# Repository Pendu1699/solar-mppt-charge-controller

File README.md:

# solar-mppt-charge-controller
ESP32-based solar MPPT charge controller, custom PCB, perturb &amp; observe tracking algorithm, logged efficiency test data.

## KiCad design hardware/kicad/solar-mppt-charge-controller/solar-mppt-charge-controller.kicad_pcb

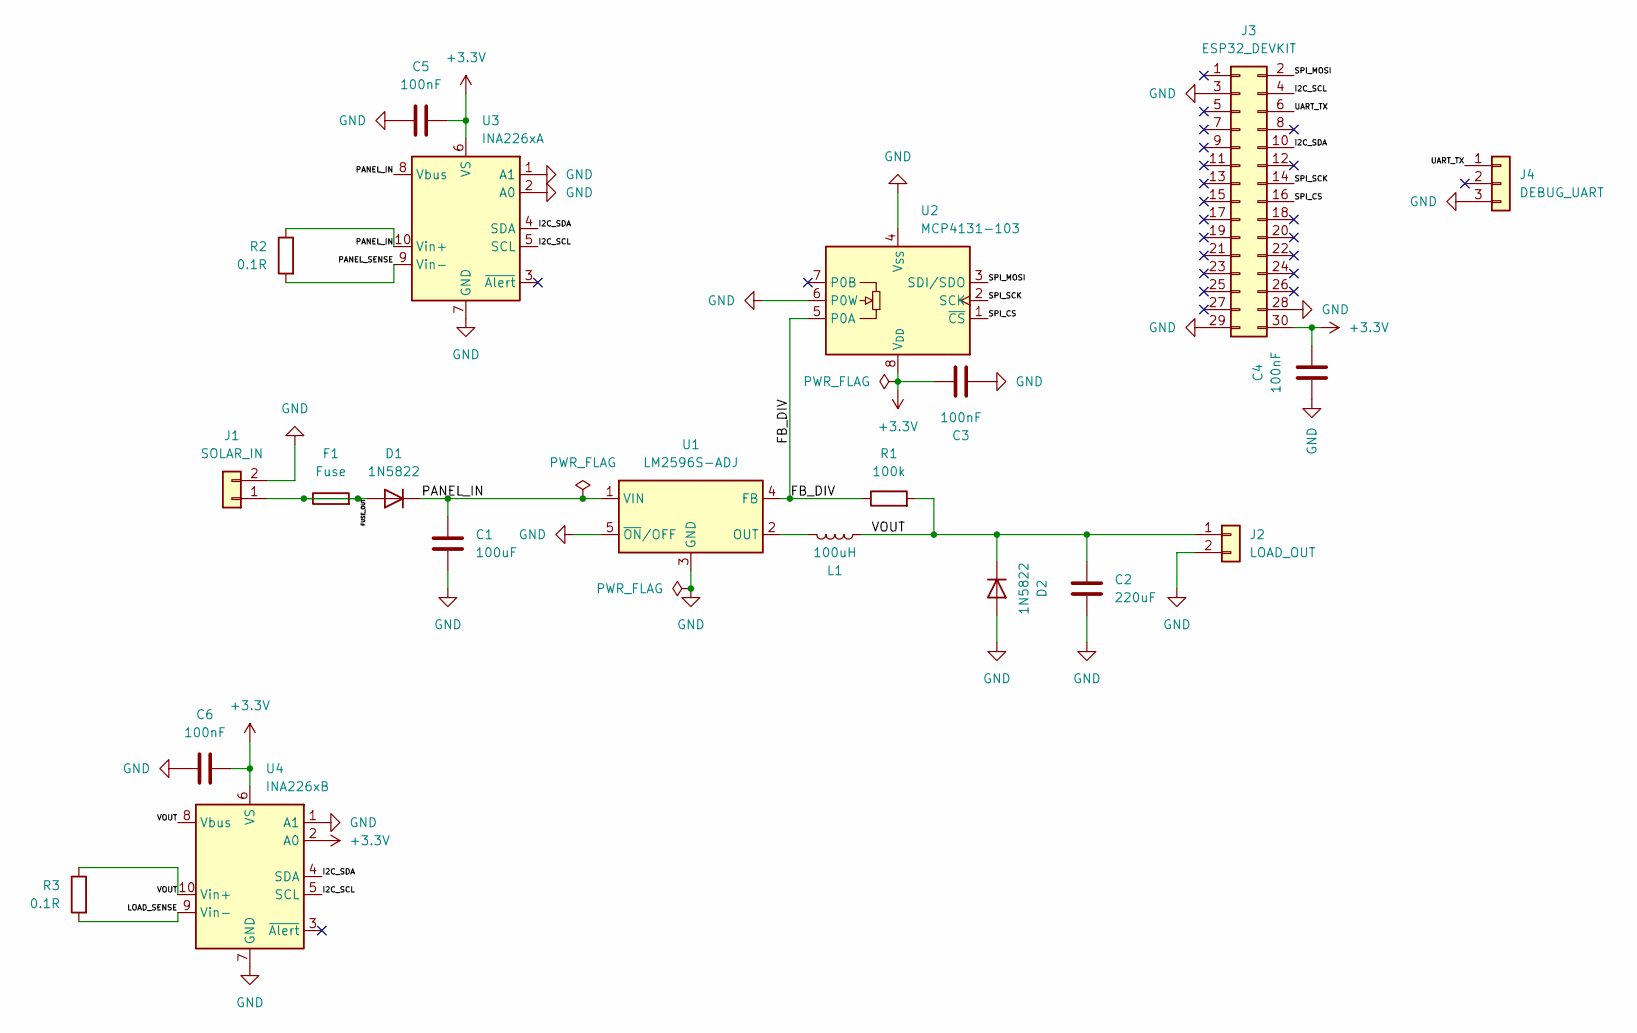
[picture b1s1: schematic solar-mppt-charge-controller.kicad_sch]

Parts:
C1: 100uF; C_Radial_D8.0mm_H7.0mm_P3.50mm
C2: 220uF; C_Radial_D10.0mm_H12.5mm_P5.00mm
C3, C4, C5, C6: 100nF; C_0805_2012Metric_Pad1.18x1.45mm_HandSolder
D1, D2: 1N5822; D_DO-201AD_P12.70mm_Horizontal
F1: Fuse; Fuse_1812_4532Metric_Pad1.30x3.40mm_HandSolder
J1: SOLAR_IN; PinHeader_1x02_P2.54mm_Vertical
J2: LOAD_OUT; PinHeader_1x02_P2.54mm_Vertical
J3: ESP32_DEVKIT; PinHeader_2x15_P2.54mm_Vertical
J4: DEBUG_UART; PinHeader_1x03_P2.54mm_Vertical
L1: 100uH; L_Axial_L11.0mm_D4.5mm_P15.24mm_Horizontal_Fastron_MECC
R1: 100k; R_0805_2012Metric_Pad1.20x1.40mm_HandSolder
R2, R3: 0.1R; R_2512_6332Metric_Pad1.40x3.35mm_HandSolder
U1: LM2596S-ADJ; TO-263-5_TabPin3
U2: MCP4131-103; DIP-8_W7.62mm
U3: INA226xA; SOIC-10_3.9x4.9mm_P1mm
U4: INA226xB; SOIC-10_3.9x4.9mm_P1mm

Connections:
+3.3V: C3.2, C4.2, C5.2, C6.2, J3.30, U2.8 (V_{DD}), U3.6 (VS), U4.2 (A0), U4.6 (VS)
/FB_DIV: R1.1, U1.4 (FB), U2.5 (P0A)
/FUSE_OUT: D1.2 (A), F1.1, F1.2, J1.1
/I2C_SCL: J3.4, U3.5 (SCL), U4.5 (SCL)
/I2C_SDA: J3.10, U3.4 (SDA), U4.4 (SDA)
/LOAD_SENSE: R3.2, U4.9 (Vin-)
/PANEL_IN: C1.2, D1.1 (K), R2.1, U1.1 (VIN), U3.8 (Vbus), U3.10 (Vin+)
/PANEL_SENSE: R2.2, U3.9 (Vin-)
/SPI_CS: J3.16, U2.1 (~CS)
/SPI_MOSI: J3.2, U2.3 (SDI/SDO)
/SPI_SCK: J3.14, U2.2 (SCK)
/UART_TX: J3.6, J4.1
/VOUT: C2.1, D2.1 (K), J2.1, L1.1, R1.2, R3.1, U4.8 (Vbus), U4.10 (Vin+)
GND: C1.1, C2.2, C3.1, C4.1, C5.1, C6.1, D2.2 (A), J1.2, J2.2, J3.3, J3.28, J3.29, J4.3, U1.3 (GND), U1.5 (~ON/OFF), U2.4 (V_{SS}), U2.6 (P0W), U3.1 (A1), U3.2 (A0), U3.7 (GND), U4.1 (A1), U4.7 (GND)
unnamed: L1.2, U1.2 (OUT)

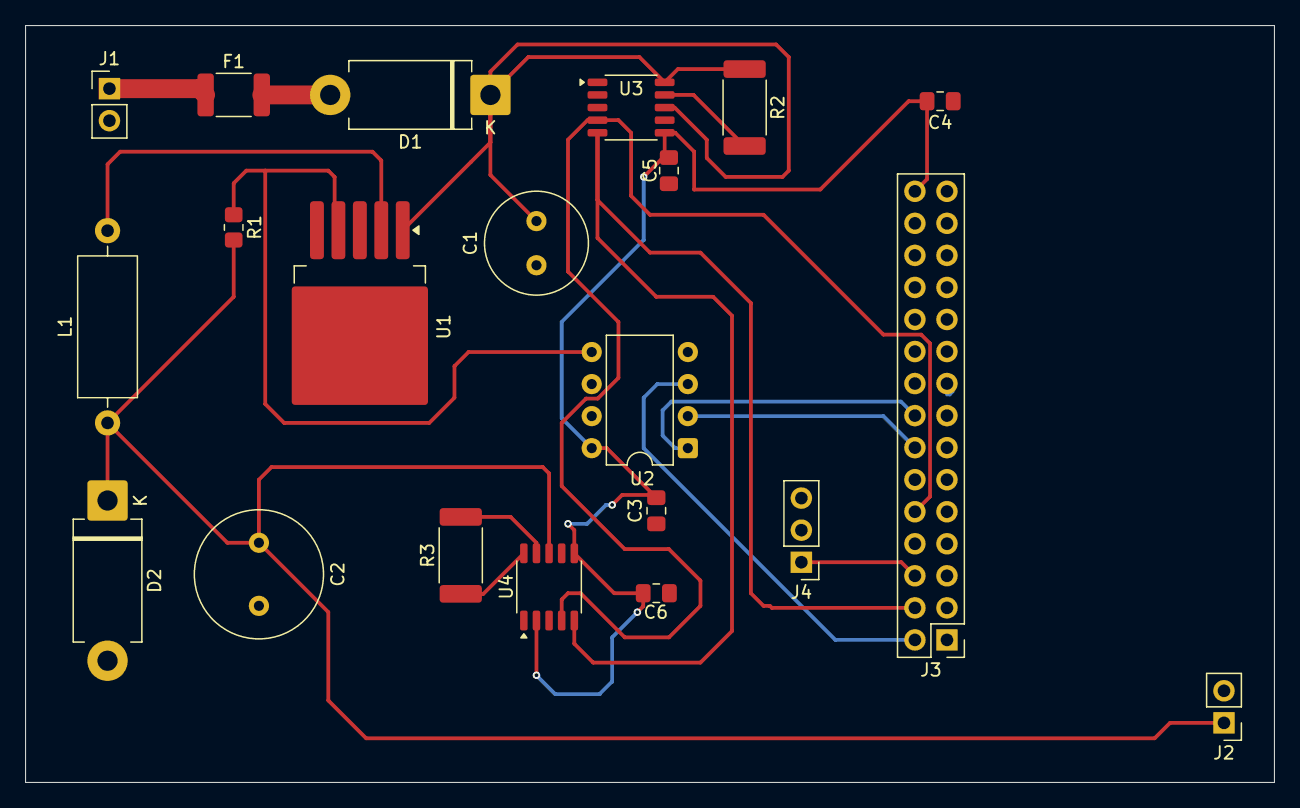
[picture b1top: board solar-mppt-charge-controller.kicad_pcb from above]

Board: 2 copper layers, 99.0 x 60.0 mm, 21 parts (0 on the bottom side), 15 nets.

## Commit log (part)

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2026-06-24 Set up project folder structure
